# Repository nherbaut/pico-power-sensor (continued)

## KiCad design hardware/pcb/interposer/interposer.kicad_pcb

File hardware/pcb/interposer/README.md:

# Pi 5 power-and-sensing interposer — rev A draft

This package implements the agreed power entry, fuse, four-terminal shunt and HAT pass-through. The sensor and Pico stay off-board.

## Electrical schematic

The drawing below is exported from the current KiCad electrical schematic. Matching net names are electrical connections; the schematic uses named nets rather than long wires across the sheet. Click the PNG to inspect component labels and pin numbers at full resolution.

[Open full-size schematic PNG](schematic.png) · [Download schematic PDF](schematic.pdf).

## Front PCB layout

[Open full-size PCB PNG](layout-front.png) · [Original front SVG](layout-front.svg).

## Design files

- [Circuit source](circuit.json): pin-to-net mapping, parts, placement and electrical defaults.
- [KiCad schematic](interposer.kicad_sch): self-contained symbols; electrical connections use named nets.
- [KiCad PCB](interposer.kicad_pcb): routed two-layer review board, with explicit power paths and ground pours.
- [Project configuration](interposer.kicad_pro).
- [Electrical schematic PDF](schematic.pdf).
- [Power-path overview](schematic.svg).
- [Front copper preview](layout-front.svg) and [back copper preview](layout-back.svg), both viewed from above.
- [Portable review archive](interposer-review.zip).
- [ERC report](checks/erc.rpt), [DRC and schematic parity report](checks/drc.rpt), [source calculations](checks/source-check.json).
- [Mechanical placement preview](placement.svg).
- [Pin assignments](pinout.csv).
- [Board BOM](board-bom.csv).
- [PNG export provenance](images.json): source CAD hashes and image dimensions.

The complete generated board is reproducible with `make hardware-build`; this needs KiCad 9, its distribution Python module and NumPy. `make hardware-generate` alone resets it to an unrouted placement. `make hardware-export` runs checks and exports review artifacts. **Do not regenerate over hand-edited KiCad files without saving the edits.** The generator defines the circuit; native KiCad footprints are then placed, routing is generated, and net names are synchronized with the schematic. Before making interactive changes, preserve this generated version and use the KiCad files as the authoritative design. The exported placement diagram is a provisional geometry guide; use the copper previews for actual native footprints.

## Electrical choices

`J1 -> F1 -> Q1/Q2 -> RSH1 -> J2 pins 2/4` is the only positive DUT supply path. The eight Pi ground pins share the return. The socket and upper male pins are one continuous stacking connector, not two independently wired connectors.

- RSH1: Vishay WSK25125L000DEA, 5 mOhm, 0.5%, 1 W, four terminals. Pads 1/4 carry current; pads 2/3 are the Kelvin sense connections. No copper may bridge around the resistor.
- Protection: LTC4367IMS8#PBF and two source-to-source BSC010N04LS6 MOSFETs. All control supply, threshold divider and gate-slew circuitry is upstream of the shunt. This option is the recommended default from the pending protection preference; it can be revised before layout release.
- Divider: 95.3 kOhm from fused input to UV, 1.50 kOhm from UV to OV, 10.0 kOhm from OV to ground; all 0.1%. Nominal falling UV trip is 4.643 V, rising OV trip 5.340 V. Comparator tolerance, hysteresis and leakage must be included in the acceptance report. These are input-fault cutoffs, not precision output clamps or proof of the Pi's permissible voltage envelope.
- The controller's VOUT sensing is connected to PROTECTED, before the shunt, so its current is excluded from DUT current. An input-rated 100 nF capacitor is also before the shunt.
- R5 pulls SHDN up through 510 kOhm to limit reverse-input pin current. R6/R7 are 10 Ohm individual gate resistors. R8/C1 form the 5.1 kOhm / 12 nF gate slew branch recommended for review against the reference circuit and actual Pi inrush.
- F1: initial 6.3 A fast cartridge candidate in a Schurter OGN 0031.8201 holder. The fuse's DC suitability, cold resistance, power acceptance and time-current curve must be confirmed before release. With the Korad limited to 5 A, the fuse may never open during a short: supply current limiting is the primary bench short-circuit response. A fuse does not provide electronic current limiting.
- D1: Kingbright APT2012LZGCK low-current green 0805 LED, with R9 = 2.7 kOhm, 1%, at least 0.125 W. Branch: PROTECTED -> R9 -> D1 anode (pad 2); D1 cathode (pad 1) -> GND. It indicates voltage after the protection switches, before the shunt, so LED current is excluded from measured DUT current. Estimated nominal current is about 1 mA; brightness must be checked on the assembled board. It is not a Pi boot, workload or accurate voltage-valid indicator and may fade rather than switch sharply at low voltage.
- U2: TI SN74AXC4T245PWR, TSSOP-16, dual-supply fixed-direction UART/marker buffer. VCCA uses PICO_3V3 from J4 pin 5; VCCB uses PI_3V3. They share ground but never join their supply rails. C3/C4 are 100 nF X7R/16 V/0805 decouplers. R10-R15 are 100 kOhm/1%/0805, providing local UART idle-high and marker idle-low bias. Both banks are enabled; bank 1 DIR is low (Pi -> Pico), bank 2 DIR is high (Pico -> Pi). Unused input is grounded and unused output is unconnected.
- The buffer's Pi-side supply and bias consumption are an explicitly accepted instrumentation overhead **included** in measured DUT current. Characterize static and traffic-dependent energy; do not assume it is excluded or subtract a constant. Power-off isolation is designed for either rail below 100 mV; brownout/rail decay and both power orders still need bench validation. It is not galvanic isolation.
- J4 is a five-pin JST-XH UART connector, distinct from four-pin J3. [Wiring](../../../docs/wiring.md) defines the changed harness pinout and Pico 3V3 supply input. Four-pin UART harnesses cannot be reused.
- No resettable PTC or regulator is included.

## Mechanical choices

The main body is 66 x 46 mm, with a small right mounting extension giving a 67.13 x 46 mm envelope and a component-free header band; the populated side wing extends outward from the GPIO edge. All dimensions are provisional pending physical fit. No tall component is placed inside the Pi/cooler footprint in the intended orientation.

H1 and H2 are board-only 2.7 mm non-plated mounting holes for provisional M2.5 hardware. Their centers are (5.13, 41.27) and (63.13, 41.27) mm from the PCB top-left, 58 mm apart. Both have a 6 mm diameter keepout for tracks, vias and copper pours on both sides. They are intentionally absent from the electrical schematic and component BOM; the mounting hardware is covered by HW-028. The right edge extends locally to x=67.13 mm from y=37 to 46 mm, providing 4 mm from H2 center to the outside edge.

The header-to-hole offsets (-4.87, -1.27) and (53.13, -1.27) mm relative to J2 pin 1 are provisional mechanical geometry, cross-checked against the installed KiCad Raspberry Pi Zero socketed mounting-hole footprint and the 58 mm standard mounting spacing. This is not a measured Pi 5 fit. Verify center positions, full socket body, screw-head/washer diameters and spacer engagement on the actual Pi 5. Maximum planned hardware envelope is 6 mm diameter; larger washers require a new clearance review. Split lower/upper standoffs must match connector seating without PCB flex; retain strain relief on the power harness.

J2 is a Samtec SSQ-120-03-G-D candidate with 10 mm tails used as the upper male pass-through. Pins are 2.54 mm pitch. Verify socket mating depth, tail protrusion through the chosen 1.6 mm PCB, orientation and the AI HAT's mating socket. Samtec quotes 6.3 A per contact for an SSQ/TSW test pair; that is **not an all-contacts-loaded Pi-header guarantee**. Verify derating, sharing between the two positive contacts, contact resistance and temperature at 5 A.

J1 uses Phoenix Contact MSTB 2,5/2-GF-5,08 1776508 with screw-flanged mating plug 1777989. It is polarized and secured after wiring. Verify footprint dimensions and flange hardware from the current manufacturer drawing. Avoid generic unverified connector substitutions.

The side wing needs external support and cable strain relief: do not use the Pi header as the only mechanical support. A physical mock-up must establish spacer heights, cooler clearance and PCIe cable reach for AI HAT+ and AI HAT+ 2. The Raspberry Pi mechanical drawing is explicitly approximate and must not be used alone as production data.

## Release status

**Routed engineering draft, not fabrication-ready.** KiCad 9.0.9 reports zero ERC violations, zero DRC violations, zero unconnected pads and zero schematic parity issues. Thirteen source-invariant tests pass. These are automated design checks, not bench validation. There are no released Gerbers. Re-run `make hardware-export` after changes to update checks and previews.

The stackup records 1.6 mm total thickness with two 70 um copper layers. The local footprint snapshots come from the installed KiCad libraries; their [license](PicoPower.pretty/LICENSE.md) and provenance in `circuit.json` are retained. The custom stacking-header footprint remains subject to manufacturer and physical review.

The [CSV release checklist](../../release-checklist.csv) separates prototype fabrication checks from assembled-board validation before Pi connection. Fabrication requires circuit/footprint/power-budget/routing review, clean ERC/DRC, physical mock-up and manufacturing-package review. Connection additionally requires dummy-load thermal/drop, input-fault/inrush, interface and sensing validation. Read the [current review findings](../../review/README.md), [release procedure](../../../docs/release.md), [assembly procedure](../../../docs/assembly.md) and [acceptance protocols](../../../tests/README.md). Both gates remain blocked.

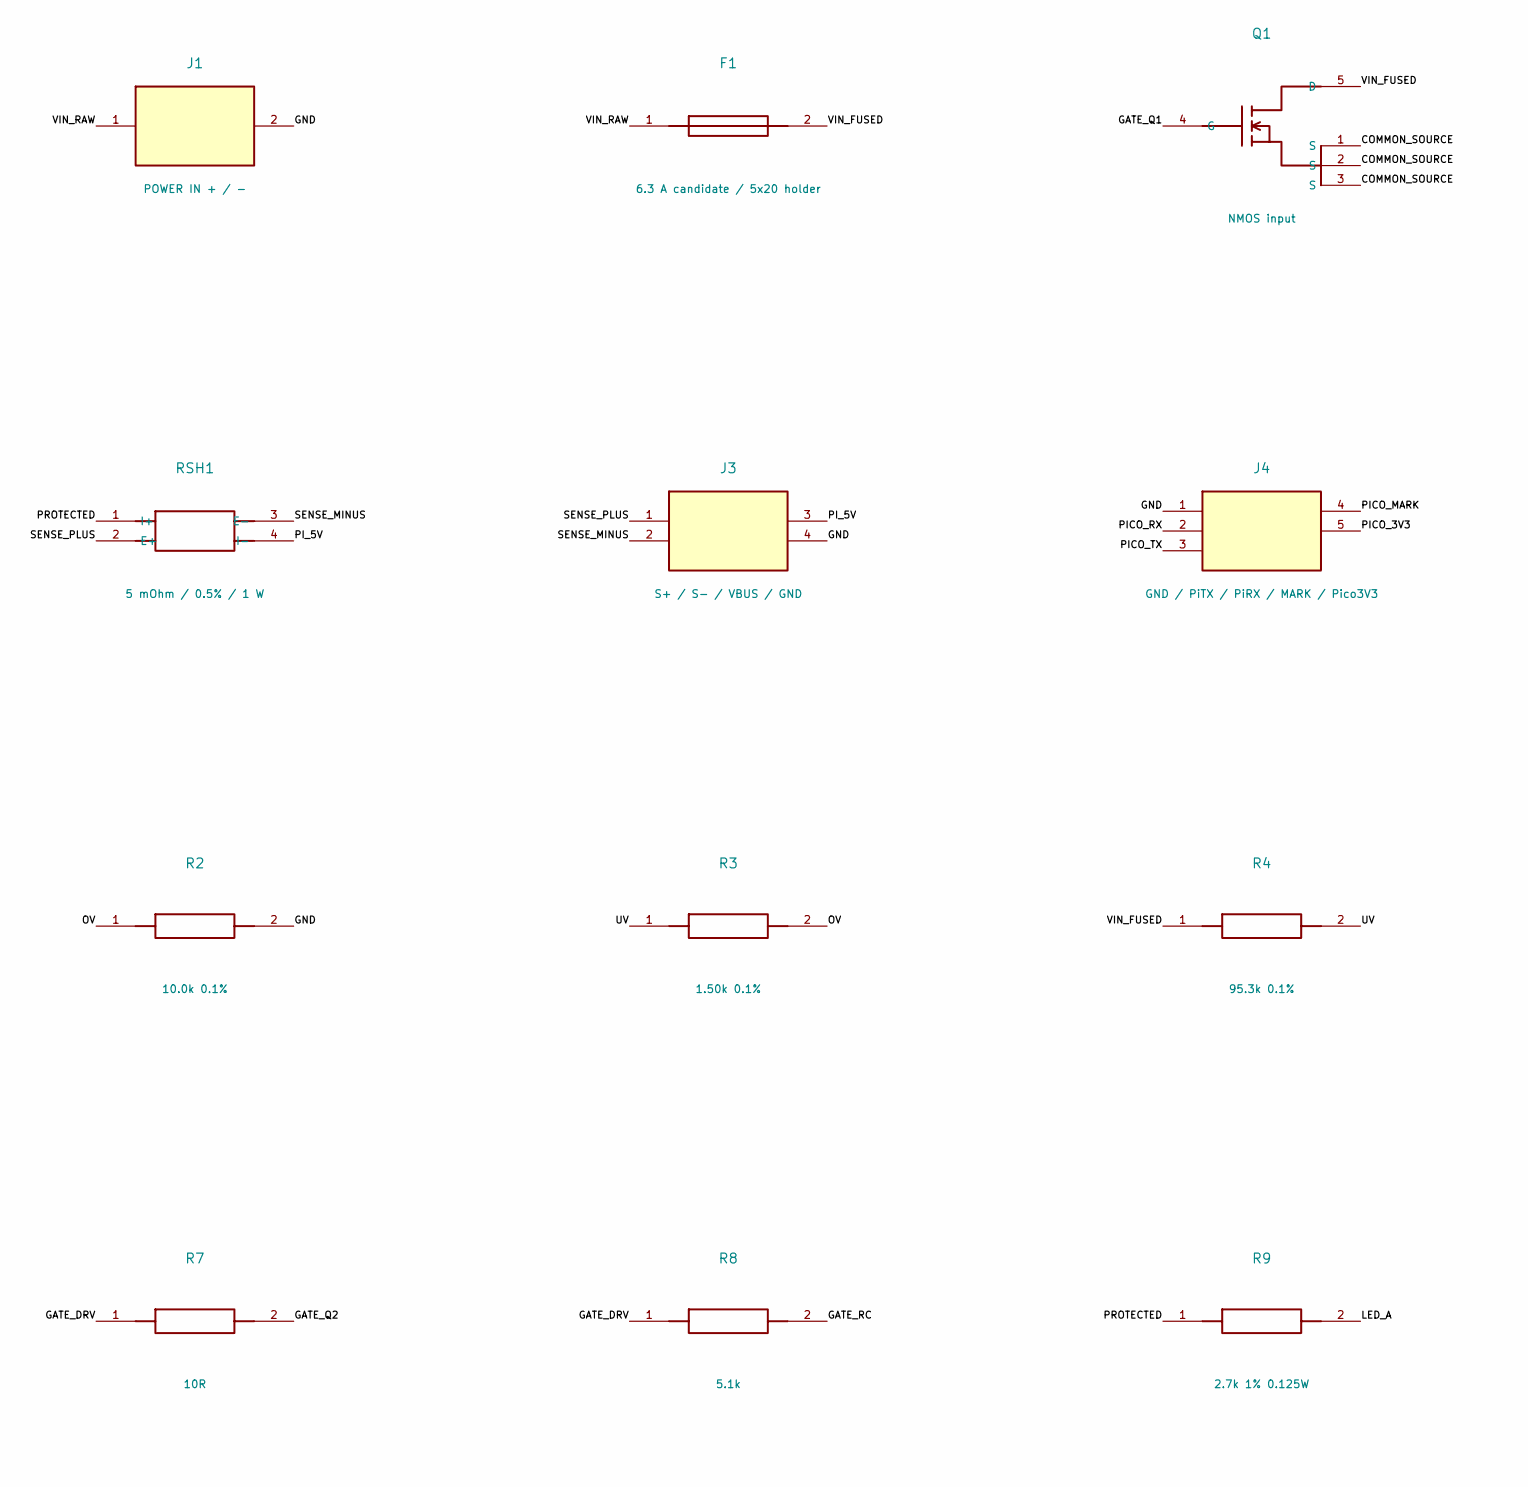
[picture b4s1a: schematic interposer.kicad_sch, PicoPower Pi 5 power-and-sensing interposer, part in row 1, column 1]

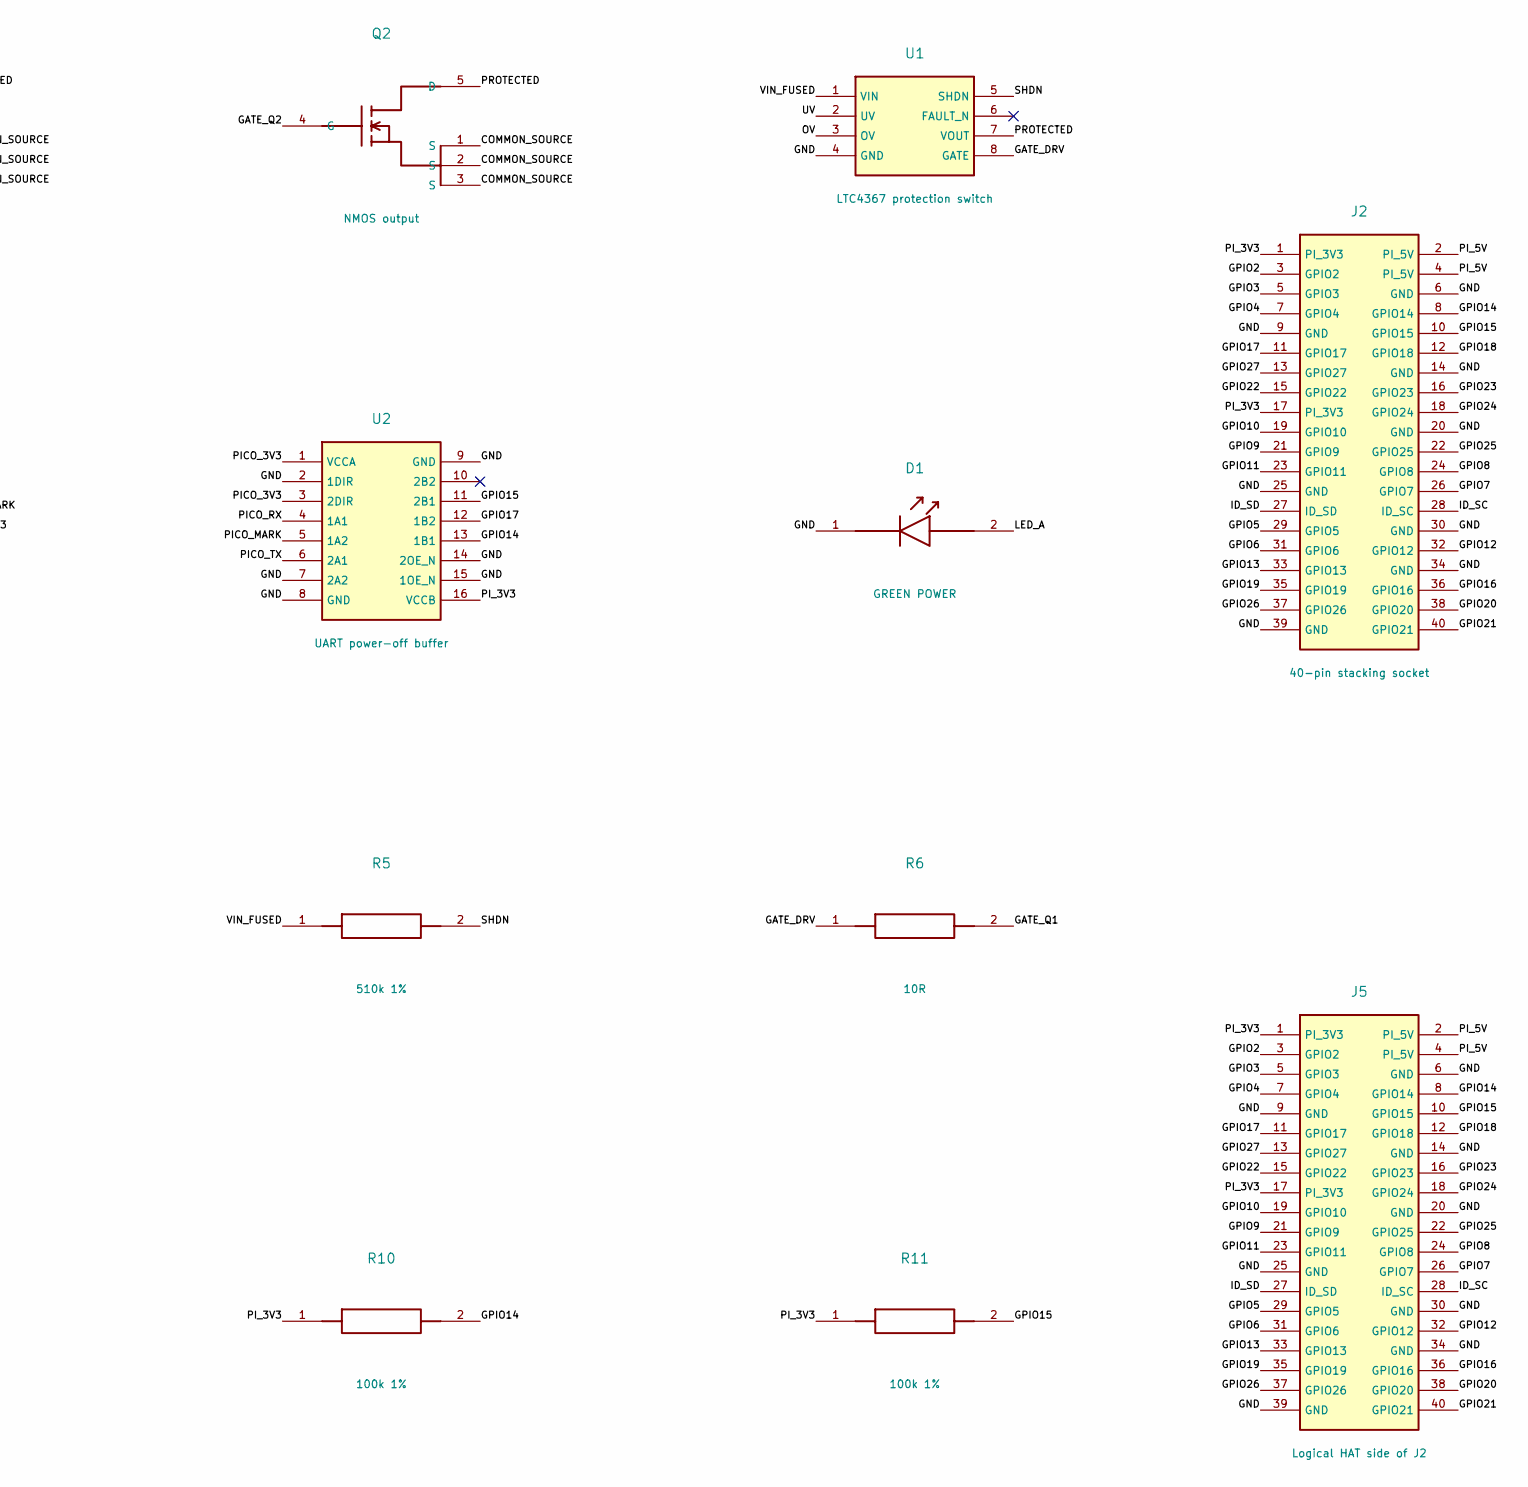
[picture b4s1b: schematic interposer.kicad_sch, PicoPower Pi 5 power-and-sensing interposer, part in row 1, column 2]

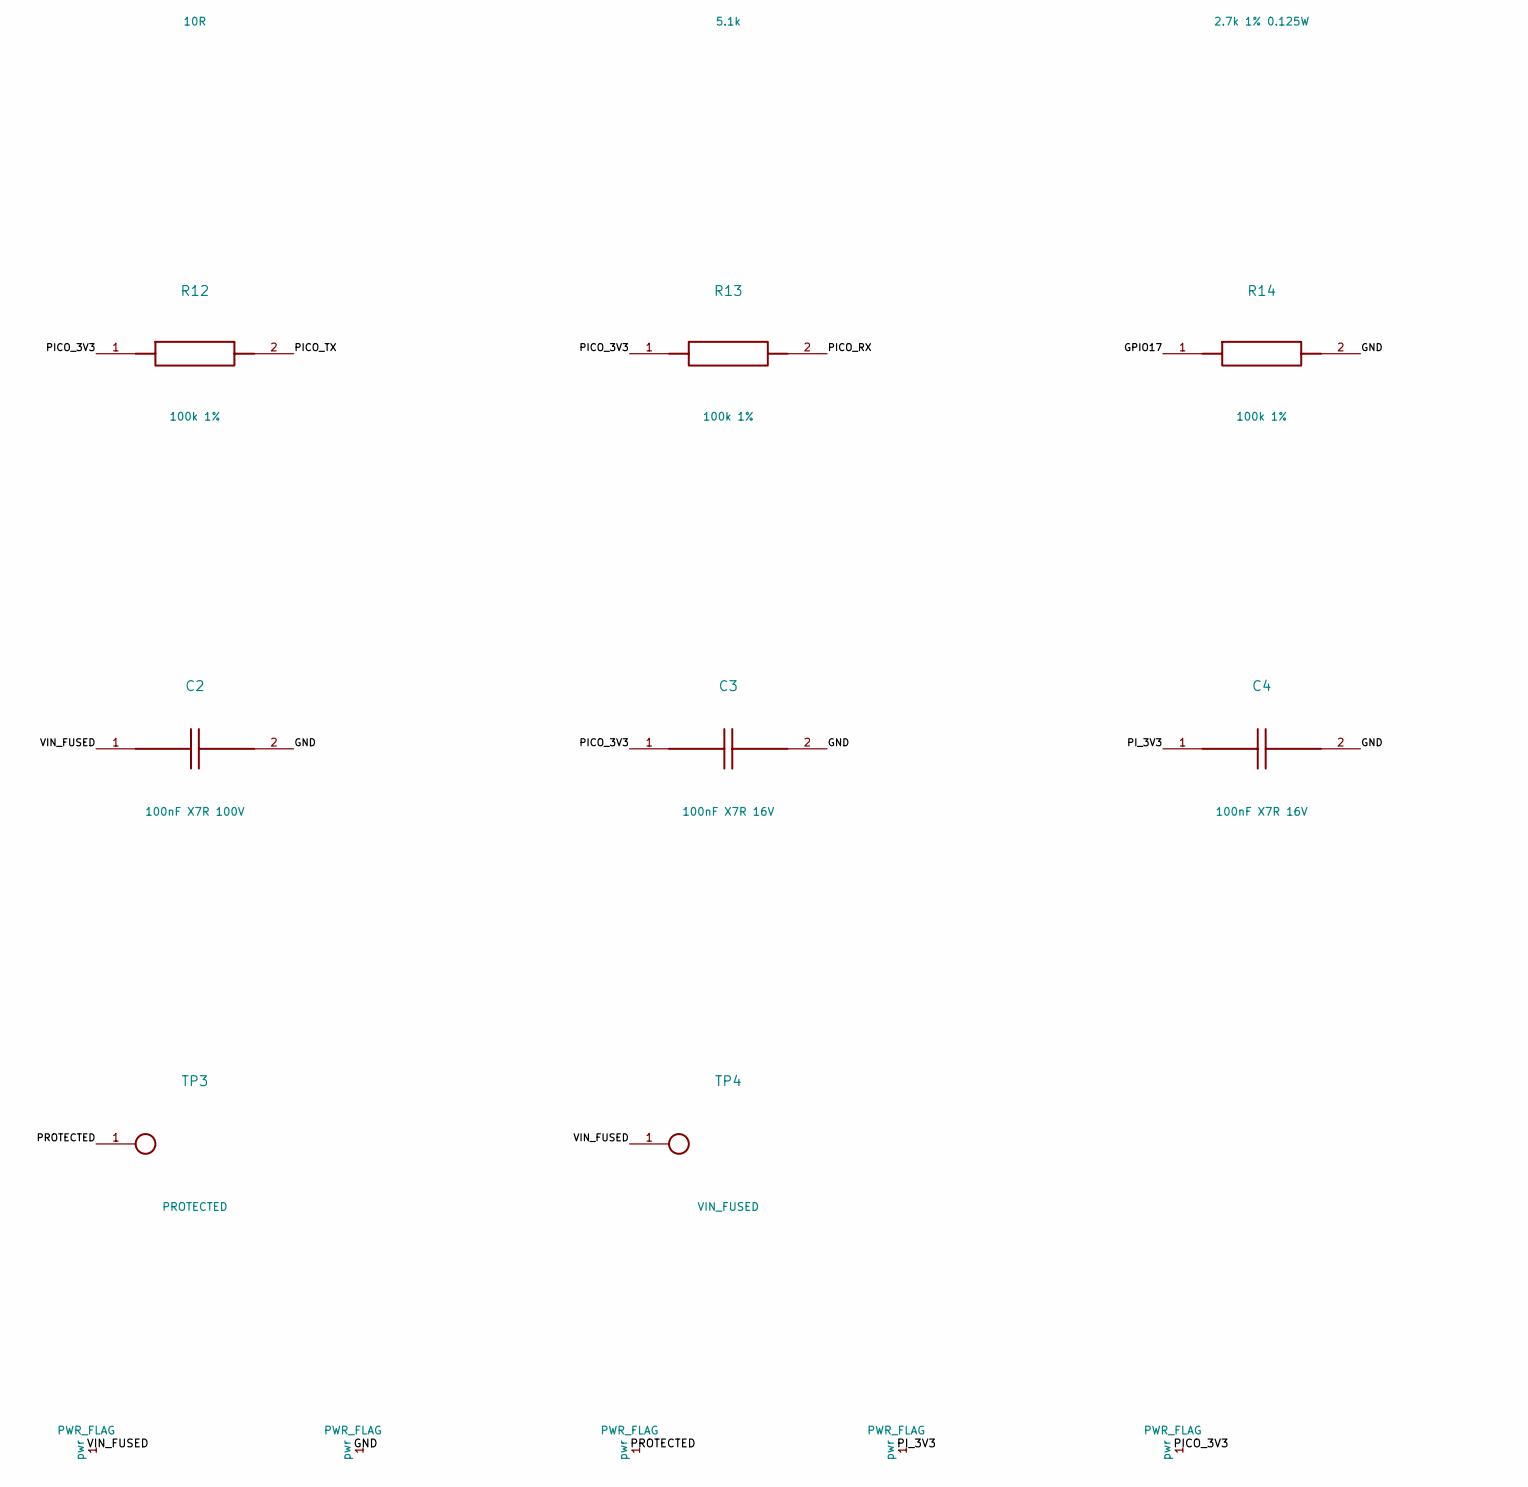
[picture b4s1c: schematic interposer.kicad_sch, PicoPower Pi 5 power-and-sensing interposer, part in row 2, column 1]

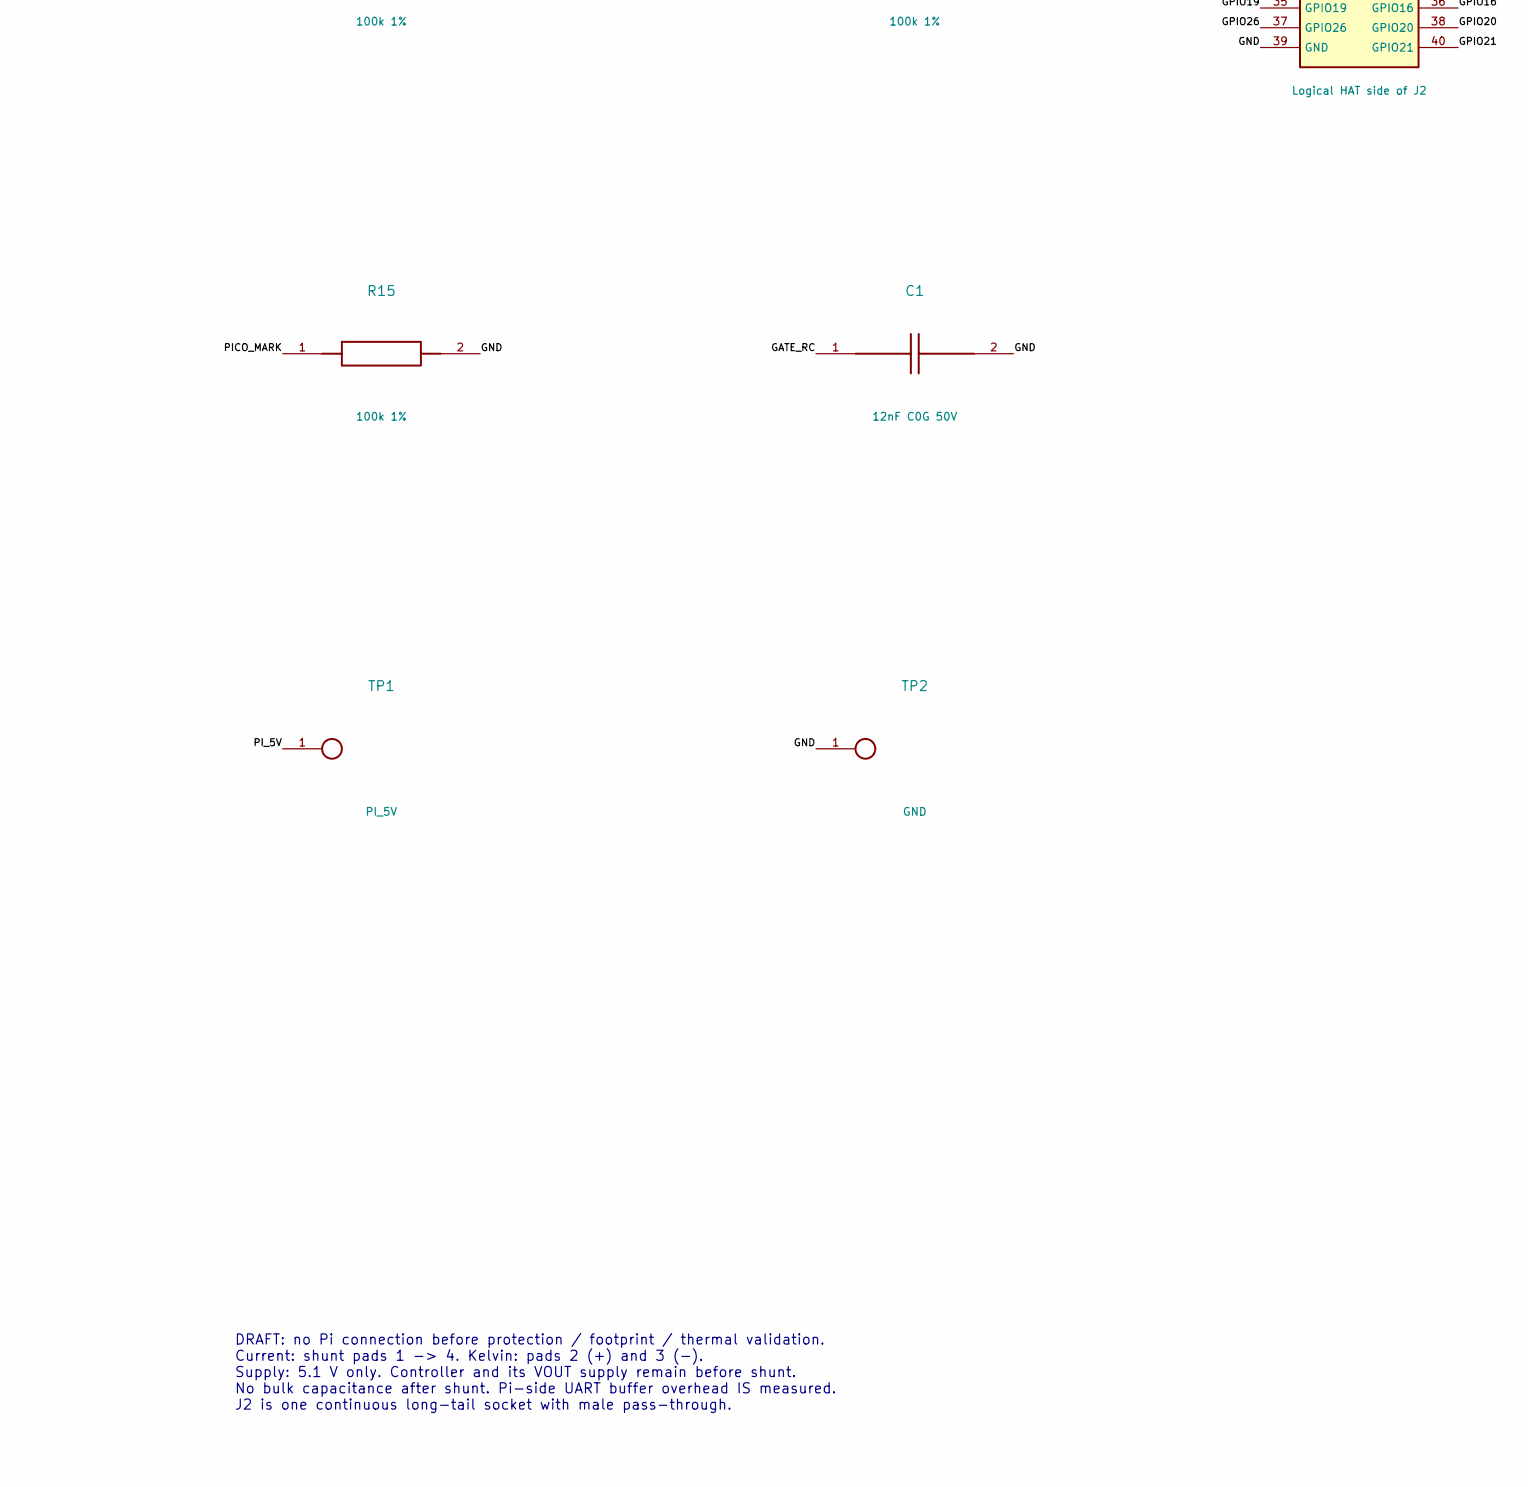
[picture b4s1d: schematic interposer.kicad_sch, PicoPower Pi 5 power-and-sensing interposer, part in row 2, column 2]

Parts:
C1: 12nF C0G 50V; C_0805_KEMET; MPN C0805C123J5GACTU
C2: 100nF X7R 100V; C_0805_Murata; MPN GRM21BR72A104JAC4L
C3, C4: 100nF X7R 16V; C_0805_Murata; MPN GRM21BR71C104KA01L
D1: GREEN POWER; LED_0805; MPN APT2012LZGCK
F1: 6.3 A candidate / 5x20 holder; Fuse_OGN_P22.5; MPN 0031.8201
J1: POWER IN + / -; Power_GF_2; MPN 1776508
J2: 40-pin stacking socket; Stack_2x20_P2.54; MPN SSQ-120-03-G-D
J3: S+ / S- / VBUS / GND; XH4_P2.5; MPN B4B-XH-A(LF)(SN)
J4: GND / PiTX / PiRX / MARK / Pico3V3; XH5_P2.5; MPN B5B-XH-A(LF)(SN)
J5: Logical HAT side of J2; Stack_2x20_P2.54
Q1: NMOS input; SuperSO8_Draft; MPN BSC010N04LS6ATMA1
Q2: NMOS output; SuperSO8_Draft; MPN BSC010N04LS6ATMA1
R2: 10.0k 0.1%; R_0805_TNPW; MPN TNPW080510K0BEEA
R3: 1.50k 0.1%; R_0805_TNPW; MPN TNPW08051K50BEEA
R4: 95.3k 0.1%; R_0805_TNPW; MPN TNPW080595K3BEEA
R5: 510k 1%; R_0805; MPN CRCW0805510KFKEA
R6, R7: 10R; R_0805; MPN CRCW080510R0FKEA
R8: 5.1k; R_0805; MPN CRCW08055K10FKEA
R9: 2.7k 1% 0.125W; R_0805; MPN CRCW08052K70FKEA
R10, R11, R12, R13, R14, R15: 100k 1%; R_0805; MPN CRCW0805100KFKEA
RSH1: 5 mOhm / 0.5% / 1 W; WSK2512_5m_Kelvin; MPN WSK25125L000DEA
TP1: PI_5V; TestPoint_Pad_2mm
TP2: GND; TestPoint_Pad_2mm
TP3: PROTECTED; TestPoint_Pad_2mm
TP4: VIN_FUSED; TestPoint_Pad_2mm
U1: LTC4367 protection switch; MSOP8_P0.65; MPN LTC4367IMS8#PBF
U2: UART power-off buffer; TSSOP16_P0.65; MPN SN74AXC4T245PWR

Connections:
/COMMON_SOURCE: Q1.1 (S), Q1.2 (S), Q1.3 (S), Q2.1 (S), Q2.2 (S), Q2.3 (S)
/GATE_DRV: R6.1 (GATE_DRV), R7.1 (GATE_DRV), R8.1 (GATE_DRV), U1.8 (GATE)
/GATE_Q1: Q1.4 (G), R6.2 (GATE_Q1)
/GATE_Q2: Q2.4 (G), R7.2 (GATE_Q2)
/GATE_RC: C1.1 (GATE_RC), R8.2 (GATE_RC)
/GND: C1.2 (GND), C2.2 (GND), C3.2 (GND), C4.2 (GND), D1.1 (K), J1.2 (GND), J2.6 (GND), J2.9 (GND), J2.14 (GND), J2.20 (GND), J2.25 (GND), J2.30 (GND), J2.34 (GND), J2.39 (GND), J3.4 (GND), J4.1 (GND), J5.6 (GND), J5.9 (GND), J5.14 (GND), J5.20 (GND), J5.25 (GND), J5.30 (GND), J5.34 (GND), J5.39 (GND), R2.2 (GND), R14.2 (GND), R15.2 (GND), TP2.1, U1.4 (GND), U2.2 (1DIR), U2.7 (2A2), U2.8 (GND), U2.9 (GND), U2.14 (2OE_N), U2.15 (1OE_N)
/GPIO2: J2.3 (GPIO2), J5.3 (GPIO2)
/GPIO3: J2.5 (GPIO3), J5.5 (GPIO3)
/GPIO4: J2.7 (GPIO4), J5.7 (GPIO4)
/GPIO5: J2.29 (GPIO5), J5.29 (GPIO5)
/GPIO6: J2.31 (GPIO6), J5.31 (GPIO6)
/GPIO7: J2.26 (GPIO7), J5.26 (GPIO7)
/GPIO8: J2.24 (GPIO8), J5.24 (GPIO8)
/GPIO9: J2.21 (GPIO9), J5.21 (GPIO9)
/GPIO10: J2.19 (GPIO10), J5.19 (GPIO10)
/GPIO11: J2.23 (GPIO11), J5.23 (GPIO11)
/GPIO12: J2.32 (GPIO12), J5.32 (GPIO12)
/GPIO13: J2.33 (GPIO13), J5.33 (GPIO13)
/GPIO14: J2.8 (GPIO14), J5.8 (GPIO14), R10.2 (GPIO14), U2.13 (1B1)
/GPIO15: J2.10 (GPIO15), J5.10 (GPIO15), R11.2 (GPIO15), U2.11 (2B1)
/GPIO16: J2.36 (GPIO16), J5.36 (GPIO16)
/GPIO17: J2.11 (GPIO17), J5.11 (GPIO17), R14.1 (GPIO17), U2.12 (1B2)
/GPIO18: J2.12 (GPIO18), J5.12 (GPIO18)
/GPIO19: J2.35 (GPIO19), J5.35 (GPIO19)
/GPIO20: J2.38 (GPIO20), J5.38 (GPIO20)
/GPIO21: J2.40 (GPIO21), J5.40 (GPIO21)
/GPIO22: J2.15 (GPIO22), J5.15 (GPIO22)
/GPIO23: J2.16 (GPIO23), J5.16 (GPIO23)
/GPIO24: J2.18 (GPIO24), J5.18 (GPIO24)
/GPIO25: J2.22 (GPIO25), J5.22 (GPIO25)
/GPIO26: J2.37 (GPIO26), J5.37 (GPIO26)
/GPIO27: J2.13 (GPIO27), J5.13 (GPIO27)
/ID_SC: J2.28 (ID_SC), J5.28 (ID_SC)
/ID_SD: J2.27 (ID_SD), J5.27 (ID_SD)
/LED_A: D1.2 (A), R9.2 (LED_A)
/OV: R2.1 (OV), R3.2 (OV), U1.3 (OV)
/PICO_3V3: C3.1 (PICO_3V3), J4.5 (PICO_3V3), R12.1 (PICO_3V3), R13.1 (PICO_3V3), U2.1 (VCCA), U2.3 (2DIR)
/PICO_MARK: J4.4 (PICO_MARK), R15.1 (PICO_MARK), U2.5 (1A2)
/PICO_RX: J4.2 (PICO_RX), R13.2 (PICO_RX), U2.4 (1A1)
/PICO_TX: J4.3 (PICO_TX), R12.2 (PICO_TX), U2.6 (2A1)
/PI_3V3: C4.1 (PI_3V3), J2.1 (PI_3V3), J2.17 (PI_3V3), J5.1 (PI_3V3), J5.17 (PI_3V3), R10.1 (PI_3V3), R11.1 (PI_3V3), U2.16 (VCCB)
/PI_5V: J2.2 (PI_5V), J2.4 (PI_5V), J3.3 (PI_5V), J5.2 (PI_5V), J5.4 (PI_5V), RSH1.4 (I-), TP1.1
/PROTECTED: Q2.5 (D), R9.1 (PROTECTED), RSH1.1 (I+), TP3.1, U1.7 (VOUT)
/SENSE_MINUS: J3.2 (SENSE_MINUS), RSH1.3 (E-)
/SENSE_PLUS: J3.1 (SENSE_PLUS), RSH1.2 (E+)
/SHDN: R5.2 (SHDN), U1.5 (SHDN)
/UV: R3.1 (UV), R4.2 (UV), U1.2 (UV)
/VIN_FUSED: C2.1 (VIN_FUSED), F1.2 (VIN_FUSED), Q1.5 (D), R4.1 (VIN_FUSED), R5.1 (VIN_FUSED), TP4.1, U1.1 (VIN)
/VIN_RAW: F1.1 (VIN_RAW), J1.1 (VIN_RAW)

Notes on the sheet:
DRAFT: no Pi connection before protection / footprint / thermal validation. Current: shunt pads 1 -> 4. Kelvin: pads 2 (+) and 3 (-). Supply: 5.1 V only. Controller and its VOUT supply remain before shunt. No bulk capacitance after shunt. Pi-side UART buffer overhead IS measured. J2 is one continuo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

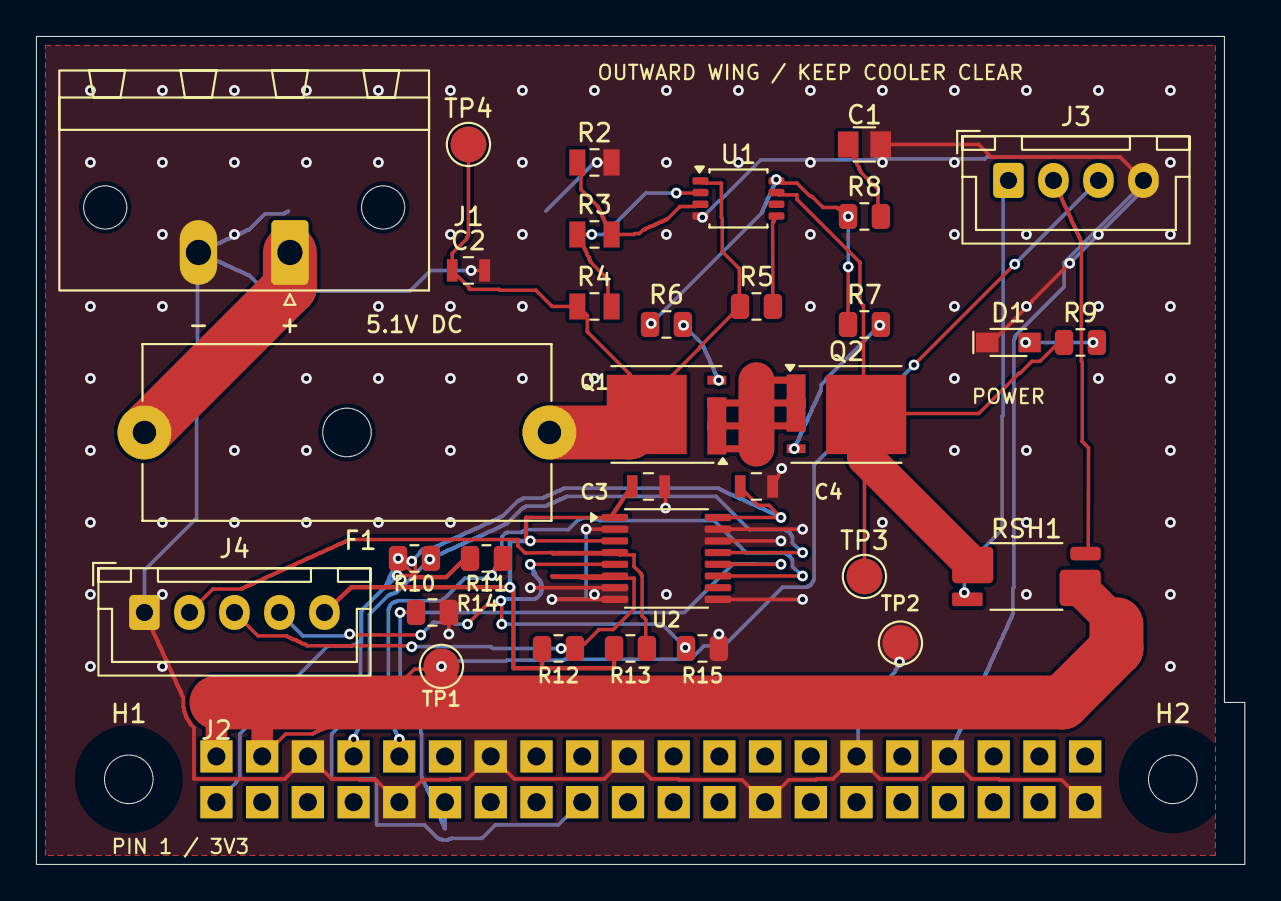
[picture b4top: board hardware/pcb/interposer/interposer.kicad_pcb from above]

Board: 2 copper layers, 67.1 x 46.0 mm, 35 parts (0 on the bottom side), 24 nets.

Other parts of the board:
H1, H2: MountingHole_2.7mm_M2.5

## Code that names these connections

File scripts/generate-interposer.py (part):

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        writer.writerows(rows)


HEADER = ['PI_3V3', 'PI_5V', 'GPIO2', 'PI_5V', 'GPIO3', 'GND',
          'GPIO4', 'GPIO14', 'GND', 'GPIO15', 'GPIO17', 'GPIO18',
          'GPIO27', 'GND', 'GPIO22', 'GPIO23', 'PI_3V3', 'GPIO24',
          'GPIO10', 'GND', 'GPIO9', 'GPIO25', 'GPIO11', 'GPIO8',
          'GND', 'GPIO7', 'ID_SD', 'ID_SC', 'GPIO5', 'GND',
          'GPIO6', 'GPIO12', 'GPIO13', 'GND', 'GPIO19', 'GPIO16',
          'GPIO26', 'GPIO20', 'GND', 'GPIO21']


def part(ref, value, mpn, footprint, pins, pos, size, url='', kind='passive'):
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    ]
    parts.append(part('U2', 'UART power-off buffer', 'SN74AXC4T245PWR', 'TSSOP16_P0.65',
                      {1:'PICO_3V3',2:'GND',3:'PICO_3V3',4:'PICO_RX',5:'PICO_MARK',
                       6:'PICO_TX',7:'GND',8:'GND',9:'GND',10:None,11:'GPIO15',
                       12:'GPIO17',13:'GPIO14',14:'GND',15:'GND',16:'PI_3V3'},
                      [35,29], [4.4,5],
                      'https://www.ti.com/lit/ds/symlink/sn74axc4t245.pdf', 'buffer'))
    parts.append(part('D1', 'GREEN POWER', 'APT2012LZGCK', 'LED_0805',
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        ('R7', '10R', 'GATE_DRV', 'GATE_Q2', [46, 16]),
        ('R8', '5.1k', 'GATE_DRV', 'GATE_RC', [46, 10]),
        ('R9', '2.7k 1% 0.125W', 'PROTECTED', 'LED_A', [58, 17]),
        ('R10', '100k 1%', 'PI_3V3', 'GPIO14', [21,29]),
        ('R11', '100k 1%', 'PI_3V3', 'GPIO15', [25,29]),
        ('R12', '100k 1%', 'PICO_3V3', 'PICO_TX', [29,34]),
        ('R13', '100k 1%', 'PICO_3V3', 'PICO_RX', [33,34]),
        ('R14', '100k 1%', 'GPIO17', 'GND', [22,32]),
        ('R15', '100k 1%', 'PICO_MARK', 'GND', [37,34]),
    ]
    for ref, value, a, b, pos in resistor_data:
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        a.append(f'<rect x="{cx-w/2}" y="{cy-h/2}" width="{w}" height="{h}" fill="#ffffff" stroke="#64748b" stroke-width=".12"/>')
        a.append(f'<text x="{cx}" y="{cy-h/2-.7}" text-anchor="middle" font-size=".9">{escape(p["ref"])}</text>')
        for n,px,py,pw,ph,drill in pads_for(name):
            net=p['pins'].get(n);col='#dc2626' if net in ['PI_5V','PROTECTED','VIN_RAW','VIN_FUSED'] else '#1e293b' if net=='GND' else '#d97706'
            a.append(f'<rect x="{x+px-pw/2}" y="{y+py-ph/2}" width="{pw}" height="{ph}" fill="{col}" opacity=".7"/>')
            if drill:a.append(f'<circle cx="{x+px}" cy="{y+py}" r="{drill/2}" fill="#fff"/>')
    for hole in data['board']['mounting_holes']:
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
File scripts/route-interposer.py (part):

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                groups.setdefault(pad.GetNetCode(),[]).append(pad)
        # Power paths are already connected; attach small-signal branches only.
        skip={'VIN_RAW','COMMON_SOURCE','PICO_3V3'}
        priority=['PROTECTED','VIN_FUSED','OV','SHDN','UV','GATE_DRV','SENSE_PLUS','SENSE_MINUS','PICO_3V3','GPIO17','GPIO15','GPIO14','PICO_TX','PICO_RX','PICO_MARK','PI_5V','PI_3V3','GATE_Q1','GATE_Q2','GATE_RC']
        ordered=sorted(groups.items(),key=lambda item:priority.index(item[1][0].GetNetname()) if item[1][0].GetNetname() in priority else 100)
        for net,pads in ordered:
            pads.sort(key=lambda p:(p.GetParentFootprint().GetReference()!='U1',p.GetParentFootprint().GetReference(),int(p.GetNumber())))
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
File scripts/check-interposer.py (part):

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    parts = {p['ref']: p for p in data['parts']}
    require(len(parts) == len(data['parts']), 'Duplicate reference')
    pins = {ref: p['pins'] for ref, p in parts.items()}
    require(pins['J1'] == {'1':'VIN_RAW','2':'GND'}, 'Input polarity mapping changed')
    require(pins['F1'] == {'1':'VIN_RAW','2':'VIN_FUSED'}, 'Fuse must precede protection and shunt')
    require(pins['RSH1'] == {'1':'PROTECTED','2':'SENSE_PLUS','3':'SENSE_MINUS','4':'PI_5V'},
            'Shunt must have distinct current and Kelvin nets, correct polarity')
    require(pins['U1']['1'] == 'VIN_FUSED' and pins['U1']['7'] == 'PROTECTED',
            'Controller VIN and VOUT currents must both remain upstream of shunt')
    require(pins['Q1']['1'] == pins['Q2']['1'] == 'COMMON_SOURCE', 'MOSFETs must be source-to-source')
    require(pins['Q1']['5']=='VIN_FUSED' and pins['Q2']['5']=='PROTECTED',
            'MOSFET drain orientation changed')
    require(pins['J2']['2'] == pins['J2']['4'] == 'PI_5V', 'Both Pi 5 V pins must be powered')
    ground_pins = ['6','9','14','20','25','30','34','39']
    require([n for n in pins['J2'] if pins['J2'][n]=='GND'] == ground_pins, 'Pi ground pin mapping changed')
    require(len(pins['J2']) == 40 and set(pins['J2']) == {str(n) for n in range(1,41)}, 'Header incomplete')
    require(pins['J2']['1'] == pins['J2']['17'] == 'PI_3V3', '3V3 must not be driven from input power')
    for p in parts.values():
        if p['ref'] not in ['RSH1','J2','J3','J5','TP1']:
            require('PI_5V' not in p['pins'].values(), f'{p["ref"]} adds an unintended downstream load/bypass')
        require(not (p['ref'].startswith('C') and 'PI_5V' in p['pins'].values()), 'Downstream capacitor shifts task energy')
    require(pins['J3'] == {'1':'SENSE_PLUS','2':'SENSE_MINUS','3':'PI_5V','4':'GND'}, 'Sense cable mapping changed')
    require(pins['J4'] == {'1':'GND','2':'PICO_RX','3':'PICO_TX','4':'PICO_MARK','5':'PICO_3V3'},
            'UART connector must expose buffered signals and separate Pico supply')
    expected_buffer={'1':'PICO_3V3','2':'GND','3':'PICO_3V3','4':'PICO_RX','5':'PICO_MARK',
                     '6':'PICO_TX','7':'GND','8':'GND','9':'GND','10':None,'11':'GPIO15',
                     '12':'GPIO17','13':'GPIO14','14':'GND','15':'GND','16':'PI_3V3'}
    require(pins['U2']==expected_buffer, 'Buffer rail, direction, channel or enable mapping changed')
    bias={'R10':('PI_3V3','GPIO14'),'R11':('PI_3V3','GPIO15'),
          'R12':('PICO_3V3','PICO_TX'),'R13':('PICO_3V3','PICO_RX'),
          'R14':('GPIO17','GND'),'R15':('PICO_MARK','GND')}
    for ref,(a,b) in bias.items():
        require(pins[ref]=={'1':a,'2':b} and parts[ref]['value']=='100k 1%',
                f'{ref} must bias its signal on its own power domain')
    require(pins['C3']=={'1':'PICO_3V3','2':'GND'} and pins['C4']=={'1':'PI_3V3','2':'GND'},
            'Buffer decoupling must remain on separate power domains')
    for p in parts.values():
        nets=set(p['pins'].values())
        if p['ref']!='U2':
            require(not {'PI_3V3','PICO_3V3'}<=nets, 'Independent buffer supplies are bridged')
            require(not (nets & {'GPIO14','GPIO15','GPIO17'} and nets & {'PICO_RX','PICO_TX','PICO_MARK'}),
                    'Direct signal bypass around power-off buffer')
    # A passive part may not join the load bus to any upstream supply except RSH1.
    upstream = {'VIN_RAW','VIN_FUSED','PROTECTED','COMMON_SOURCE'}
    for p in parts.values():
        nets = set(p['pins'].values())
        require(p['ref']=='RSH1' or not ('PI_5V' in nets and nets & upstream), f'Shunt bypass through {p["ref"]}')
    require(pins['D1']=={'1':'GND','2':'LED_A'}, 'LED polarity/return changed')
    require(pins['R9']=={'1':'PROTECTED','2':'LED_A'}, 'Power LED must remain upstream of shunt')
    b = data['board']
    for p in parts.values():
        x,y = p['position_mm']
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
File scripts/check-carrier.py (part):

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    parts={p['ref']:p for p in data['parts']}
    require(len(parts)==len(data['parts']),'Duplicate component reference')
    pins={ref:p['pins'] for ref,p in parts.items()}
    require(pins['J_UART']=={'1':'GND','2':'PICO_RX','3':'PICO_TX','4':'PICO_MARK','5':'PICO_3V3'},
            'Carrier connector must match interposer J4 without cable crossover')
    require(pins['J_SENSE']=={'1':'SENSE_PLUS','2':'SENSE_MINUS','3':'SENSE_VBUS','4':'GND'},
            'Sense connector must match interposer J3 without cable crossover')
    # INA229 DGS VSSOP-10 pinout, TI SLYS023A table 5-1.
    require(pins['U_PM']=={'1':'CS','2':'MOSI','3':'ALERT','4':'MISO','5':'SCLK','6':'PICO_3V3',
                           '7':'GND','8':'SENSE_VBUS','9':'SENSE_MINUS','10':'SENSE_PLUS'},
            'INA229 pin mapping, SPI, supply or sense polarity changed')
    require(parts['U_PM']['mpn']=='INA229AIDGSR','Power monitor must be the INA229 VSSOP-10')
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    for ref,p in parts.items():
        require(ref in ('J_SENSE','U_PM') or not sense&set(p['pins'].values()),
                'Analog sense connection reaches a part other than J_SENSE or U_PM (measurement boundary)')
    require(pins['C1']==pins['C2']=={'1':'PICO_3V3','2':'GND'},'Sensor 3V3 decoupling changed')
    require(pins['C_PM']=={'1':'PICO_3V3','2':'GND'},'INA229 supply bypass changed')
    require(pins['R_ALERT']=={'1':'PICO_3V3','2':'ALERT'},'INA229 open-drain ALERT needs a pull-up')
    require(pins['R_CS']=={'1':'PICO_3V3','2':'CS'},'Chip select must idle high')
    require(pins['J_SD']=={'1':'SD_DAT2','2':'SD_CS','3':'SD_MOSI','4':'SD_3V3',
                          '5':'SD_SCLK','6':'GND','7':'SD_MISO','8':'SD_DAT1','9':'GND'},
            'SD socket pinout, voltage or shield ground changed')
    require(pins['U_SD']=={'1':'USB_5V','2':'GND','3':'PICO_3V3','4':None,'5':'SD_3V3'},
            'SD regulator must use USB 5V with separate 3V3 output and Pico-powered enable')
    for n,net in {'16':'SD_MISO','17':'SD_CS','19':'SD_SCLK','20':'SD_MOSI'}.items():
        require(pico[n]==net,'SD SPI1 allocation changed')
    require({key:data['gpio'][key] for key in ['sd_spi','sd_miso','sd_cs','sd_sclk','sd_mosi']}==
            dict(sd_spi=1,sd_miso=12,sd_cs=13,sd_sclk=14,sd_mosi=15),'SD must use dedicated SPI1')
    for n,signal in enumerate(['SD_DAT2','SD_CS','SD_MOSI','SD_MISO','SD_DAT1'],1):
        require(pins[f'R_SDP{n}']=={'1':'SD_3V3','2':signal} and parts[f'R_SDP{n}']['value']=='10k 1%',
                'SD CMD and DAT0-3 require pull-ups on the SD supply domain')
    for p in parts.values():
        nets=set(p['pins'].values())
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                'SD and sensor 3V3 rails must not be bridged')
        if 'USB_5V' in nets:
            require(p['ref'] in ['J_PICO','U_SD','C_SDIN'],'Unexpected USB 5V load or bypass')
    require(pins['C_SDIN']=={'1':'USB_5V','2':'GND'},'SD LDO input decoupling changed')
    for ref in ['C_SDOUT','C_SDBULK','C_SDSOCKET']:
        require(pins[ref]=={'1':'SD_3V3','2':'GND'},'SD output decoupling changed')
    require(parts['C_SDIN']['value']==parts['C_SDOUT']['value']=='4.7uF X7R 16V',
            'SD LDO requires its specified input/output capacitors; verify effective capacitance')
    require(len(data['board']['mounting_holes'])==4,'Four mounting holes required')
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
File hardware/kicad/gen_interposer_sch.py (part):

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
# ---------------------------------------------------------------- Pi header
# Physical pin -> net, from hardware/review/pi-header-contract.csv. Pi-side
# UART/marker GPIO choice (GPIO14 TX, GPIO15 RX, GPIO23 marker) is the default
# recorded in docs/interposer-schematic.md; change it here and in that doc.
PI_PINS = {
    1: "PI_3V3", 2: "DUT_5V_POST_SHUNT", 3: "PI_GPIO2", 4: "DUT_5V_POST_SHUNT",
    5: "PI_GPIO3", 6: "BENCH_GND", 7: "PI_GPIO4", 8: "PI_GPIO14_TXD",
    9: "BENCH_GND", 10: "PI_GPIO15_RXD", 11: "PI_GPIO17", 12: "PI_GPIO18",
    13: "PI_GPIO27", 14: "BENCH_GND", 15: "PI_GPIO22", 16: "PI_GPIO23_MARKER",
    17: "PI_3V3", 18: "PI_GPIO24", 19: "PI_GPIO10", 20: "BENCH_GND",
    21: "PI_GPIO9", 22: "PI_GPIO25", 23: "PI_GPIO11", 24: "PI_GPIO8",
    25: "BENCH_GND", 26: "PI_GPIO7", 27: "PI_ID_SD_GPIO0", 28: "PI_ID_SC_GPIO1",
    29: "PI_GPIO5", 30: "BENCH_GND", 31: "PI_GPIO6", 32: "PI_GPIO12",
    33: "PI_GPIO13", 34: "BENCH_GND", 35: "PI_GPIO19", 36: "PI_GPIO16",
    37: "PI_GPIO26", 38: "PI_GPIO20", 39: "BENCH_GND", 40: "PI_GPIO21",
}

# ---------------------------------------------------------------- parts
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      "3": "DUT_VBUS_SENSE", "4": "MEAS_GND_REF"}),
    ("R5", "Device", "R", 165.1, 210.82, 90,
     "470 1%", {"MPN": "Vishay MRS25000C4700FCT00"},
     {"1": "PI_GPIO14_TXD", "2": "PI_TX_TO_PICO"}),
    ("R6", "Device", "R", 165.1, 228.6, 90,
     "470 1%", {"MPN": "Vishay MRS25000C4700FCT00"},
     {"1": "PI_GPIO23_MARKER", "2": "PI_TASK_MARKER"}),
    ("R7", "Device", "R", 165.1, 246.38, 90,
     "100k 1%", {"MPN": "Vishay MRS25000C1003FCT00"},
     {"1": "PI_GPIO15_RXD", "2": "BENCH_GND"}),
    ("NT2", "Device", "NetTie_2", 165.1, 264.16, 0,
     "NetTie", {"Note": "Single-point tie at DUT-header ground pickup"},
     {"1": "BENCH_GND", "2": "SIGNAL_GND"}),
    ("J6", "Connector_Generic", "Conn_01x05", 243.84, 228.6, 0,
     "UART/marker to carrier", {"MPN": "JST B5B-XH-A"},
     {"1": "SIGNAL_GND", "2": "PI_TX_TO_PICO", "3": "PI_GPIO15_RXD",
      "4": "PI_TASK_MARKER", "5": None}),
    ("J2", "Connector_Generic", "Conn_02x20_Odd_Even", 335.28, 134.62, 0,
     "Pi 40-pin stacking", {"MPN": "Adafruit 2223 (square-pin)"},
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    (20.32, 35.56, "Everything upstream of R1 pin 1 is outside the DUT measurement. Q1 conducts only with correct bench polarity (gate held at ground by R8); it does not block reverse current from the Pi side."),
    (20.32, 40.64, "R1 pins 2/3 are separate Kelvin pickups at the shunt lead pads; route KELVIN_* as a coupled pair, never through the 5A copper."),
    (20.32, 86.36, "Observation resistors sit at the source, before the exposed cable (docs/sense-interface-options.md). C_SENSE_DIFF (100nF) is on the carrier."),
    (20.32, 91.44, "NT1 / NT2: tie MEAS_GND_REF and SIGNAL_GND to BENCH_GND at one point next to the Pi-header ground pins."),
    (20.32, 185.42, "UART/marker (docs/uart-interface-qualification.md): 470R source resistors for Pi outputs here; Pico->Pi 470R and Pi-output 100k pull-downs are on the carrier."),
    (20.32, 190.5, "R7 (100k Pi-RX pull-down) is on the interposer. Pi GPIO choice (TX GPIO14, RX GPIO15, marker GPIO23) is a default pending AI HAT confirmation."),
    (20.32, 195.58, "The carrier pull-downs on PI_TX_TO_PICO/PI_TASK_MARKER and R7 load Pi pins under the approved UART-bias measurement-boundary exception. J6 pin 5 empty."),
    (299.72, 96.52, "J2: all 40 contacts pass through unchanged to the HAT above"),
]

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
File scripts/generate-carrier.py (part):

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                          mpn=mpn, documentation_url=url, kind=kind, rotation_deg=rotation))
    pico = {n: None for n in range(1, 41)}
    pico.update({1:'PICO_TX', 2:'PICO_RX', 4:'PICO_MARK', 5:'ALERT', 6:'MISO', 7:'CS', 9:'SCLK', 10:'MOSI',
                 32:'LED1_GPIO', 31:'LED2_GPIO', 29:'LED3_GPIO', 27:'LED4_GPIO', 26:'LED5_GPIO',
                 16:'SD_MISO',17:'SD_CS',19:'SD_SCLK',20:'SD_MOSI',
                 36:'PICO_3V3',40:'USB_5V'})
    pico.update({n:'GND' for n in [3,8,13,18,23,28,33,38]})
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                           mounting_holes=[dict(ref=f'H{i}',position_mm=pos) for i,pos in
                                           enumerate([[4,4],[62+SHIFT,4],[4,50],[62+SHIFT,50]],1)],
                           antenna_keepout_mm=[33.79+SHIFT,44.13,48+SHIFT,54]),
                gpio=dict(uart_rx=1,uart_tx=0,marker=2,alert=3,sclk=6,mosi=7,miso=4,cs=5,
                          leds=[27,26,22,21,20],sd_spi=1,sd_miso=12,sd_cs=13,sd_sclk=14,sd_mosi=15),
                storage=dict(interface='SPI1',voltage=3.3,regulator='TLV75533PDBVR',
                             supply='USB_5V',card_detect=False,firmware_status='not implemented',
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                lines.append(f'(label "{net}" (at {dx} {dy} {angle}) (effects (font (size .9 .9)) (justify {"right" if angle==0 else "left"} bottom)) (uuid "{uid("label/"+ref+"/"+n)}"))')
            else:
                lines.append(f'(no_connect (at {dx} {dy}) (uuid "{uid("nc/"+ref+"/"+n)}"))')
    # Power flags: PICO_3V3 and GND are driven by passive Pico module pins.
    for i,net in enumerate(['PICO_3V3','GND']):
        fx,fy=[round(v/1.27)*1.27 for v in (30+35*i,385)];ref=f'#FLG0{i+1}'
        lines += [f'(symbol (lib_id "Carrier:SupplyFlag") (at {fx} {fy} 0) (unit 1) (in_bom no) (on_board no) (dnp no) (uuid "{uid(ref)}")',
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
